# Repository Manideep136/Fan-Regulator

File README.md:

# Fan-Regulator

# Fan Regulator PCB Using KiCad

## 📌 Project Overview

This project involves designing a **Fan Regulator Circuit PCB** using KiCad. The circuit controls the speed of an AC fan by varying the power delivered to the fan using a TRIAC-based phase-control technique.

The design uses a DIAC, a TRIAC, a potentiometer, resistors, and capacitors to control the TRIAC triggering point during each AC cycle. By adjusting the potentiometer, the fan speed can be changed.

This project helps in understanding power electronics, AC phase control, schematic design, footprint assignment, and PCB layout.

## 🎯 Objectives

* Design an AC fan regulator circuit.
* Understand DIAC and TRIAC operation.
* Control fan speed using phase-angle control.
* Learn potentiometer-based adjustment.
* Create the schematic using KiCad.
* Assign footprints to electronic components.
* Design and route the PCB.
* Perform Electrical Rules Check (ERC) and Design Rules Check (DRC).
* View the completed PCB using KiCad's 3D Viewer.

## ⚙️ Working Principle

The fan regulator operates using the **TRIAC phase-control method**.

1. The AC supply voltage is applied to the regulator circuit.
2. A resistor-capacitor timing network charges during each AC half-cycle.
3. The potentiometer adjusts the charging time of the capacitor.
4. When the capacitor voltage reaches the DIAC's breakover voltage, the DIAC conducts.
5. The DIAC delivers a triggering pulse to the TRIAC gate.
6. The TRIAC conducts for the remainder of that AC half-cycle, supplying power to the fan.
7. Adjusting the potentiometer changes the TRIAC firing angle and therefore changes the power delivered to the fan.

**Note:** The exact speed-control range depends on the circuit design and the type of fan. Some modern electronic fans are not compatible with TRIAC phase control.

## 🧩 Components Used

| Reference | Component            | Function                         |
| --------- | -------------------- | -------------------------------- |
| D1        | DIAC (e.g., DB3)     | Triggers the TRIAC               |
| Q1        | TRIAC (e.g., BT136)  | Controls AC power                |
| RV1       | Potentiometer        | Adjusts the triggering point     |
| R1, R2    | Resistors            | Limit current and control timing |
| C1        | Capacitor            | Timing network                   |
| J1        | AC input connector   | Connects the AC supply           |
| J2        | Fan output connector | Connects the fan                 |

*The component values and ratings must match the actual schematic and the intended fan load.*

## 🔌 Block Diagram

```text
       AC Supply
           |
           v
     Timing Network
    (R + C + RV1)
           |
           v
          DIAC
           |
           v
      TRIAC Gate
           |
           v
   AC Fan Power Control
           |
           v
       AC Fan
```

## 🖥️ PCB Design Using KiCad

The PCB design process includes:

1. Creating the circuit schematic.
2. Adding the DIAC, TRIAC, potentiometer, resistors, and capacitor.
3. Connecting the components according to the circuit diagram.
4. Assigning suitable footprints based on the physical components.
5. Updating the PCB from the schematic.
6. Arranging the components on the PCB.
7. Routing the copper tracks.
8. Running ERC in the schematic editor.
9. Running DRC in the PCB editor.
10. Inspecting the final PCB using the 3D Viewer.

## 🔍 PCB Design Considerations

* Select footprints that match the actual DIAC, TRIAC, and potentiometer.
* Verify the TRIAC pinout using its datasheet.
* Choose resistors and capacitors with suitable voltage and power ratings.
* Use a capacitor specifically rated for its intended AC circuit position.
* Ensure adequate PCB creepage and clearance for mains voltage.
* Use suitable track widths and connectors for the fan current.
* Keep low-voltage control or accessible parts appropriately isolated from hazardous mains circuits where required.

## ✅ Advantages

* Provides adjustable fan speed.
* Uses a relatively simple electronic control circuit.
* Demonstrates practical DIAC and TRIAC applications.
* Helps develop PCB design and power-electronics skills.
* Can be adapted to compatible AC loads with a properly rated design.

## ⚠️ Safety Precautions

**This circuit may operate directly from hazardous AC mains voltage.** Its components and PCB tracks must be treated as live unless suitable isolation is provided.

* Do not touch the PCB while it is powered.
* Disconnect the supply before making adjustments or measurements.
* Do not connect a grounded oscilloscope directly to a live mains circuit.
* Use appropriate fusing, insulation, enclosure, creepage, and clearance.
* Have the design reviewed by a qualified person before connecting it to mains voltage.
* Confirm that the regulator is suitable for the specific fan type and current rating.

For initial learning, study the circuit using simulation or an appropriately isolated, low-voltage setup.

## 🚀 Future Improvements

* Add an insulated rotary control knob.
* Improve PCB layout and thermal management.
* Add appropriate input protection.
* Optimize the timing network for a compatible fan.
* Add a properly designed enclosure.
* Simulate the circuit before manufacturing the PCB.

## 📚 Learning Outcomes

Through this project, I learned:

* DIAC and TRIAC working principles.
* AC phase-angle control.
* Potentiometer-based adjustment.
* Timing networks using resistors and capacitors.
* Schematic design in KiCad.
* Footprint assignment.
* PCB component placement and routing.
* ERC and DRC verification.
* PCB design considerations for power electronics.

## 🛠️ Software Used

* **KiCad 9.0**

## 📄 License

This project is intended for educational purposes. The circuit should be reviewed and validated for electrical safety before practical use.

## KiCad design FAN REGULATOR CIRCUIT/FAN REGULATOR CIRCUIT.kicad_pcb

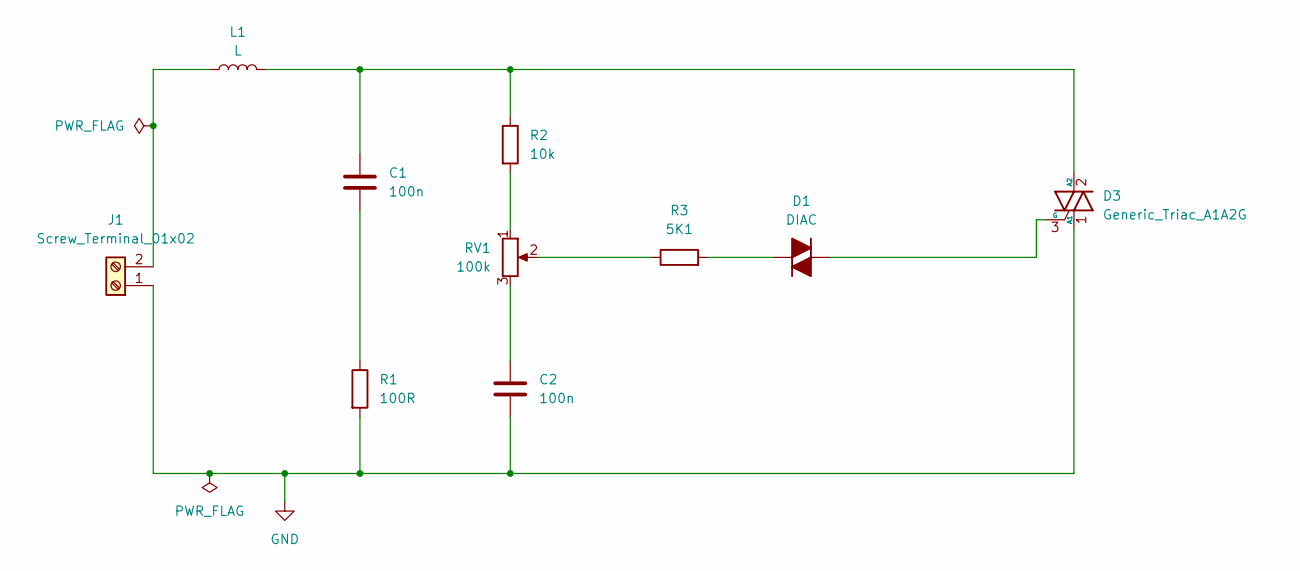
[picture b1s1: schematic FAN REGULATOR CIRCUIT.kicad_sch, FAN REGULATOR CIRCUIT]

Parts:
C1, C2: 100n; CP_Radial_D4.0mm_P1.50mm
D1: DIAC; D_DO-35_SOD27_P7.62mm_Horizontal
D3: Generic_Triac_A1A2G; TO-220-3_Vertical
J1: Screw_Terminal_01x02; TerminalBlock_Phoenix_MKDS-1,5-2-5.08_1x02_P5.08mm_Horizont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
L1: L; L_Axial_L12.8mm_D5.8mm_P5.08mm_Vertical_Fastron_HBCC
R1: 100R; R_Axial_DIN0204_L3.6mm_D1.6mm_P7.62mm_Horizontal
R2: 10k; R_Axial_DIN0204_L3.6mm_D1.6mm_P7.62mm_Horizontal
R3: 5K1; R_Axial_DIN0204_L3.6mm_D1.6mm_P7.62mm_Horizontal
RV1: 100k; Potentiometer_Alps_RK09K_Single_Horizontal

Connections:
GND: C2.2, D3.1 (A1), J1.1, R1.2
unnamed: C1.2, R1.1
unnamed: C2.1, RV1.3
unnamed: D1.2 (A), D3.3 (G)
unnamed: D1.1 (K), R3.2
unnamed: C1.1, D3.2 (A2), L1.2, R2.1
unnamed: J1.2, L1.1
unnamed: R2.2, RV1.1
unnamed: R3.1, RV1.2

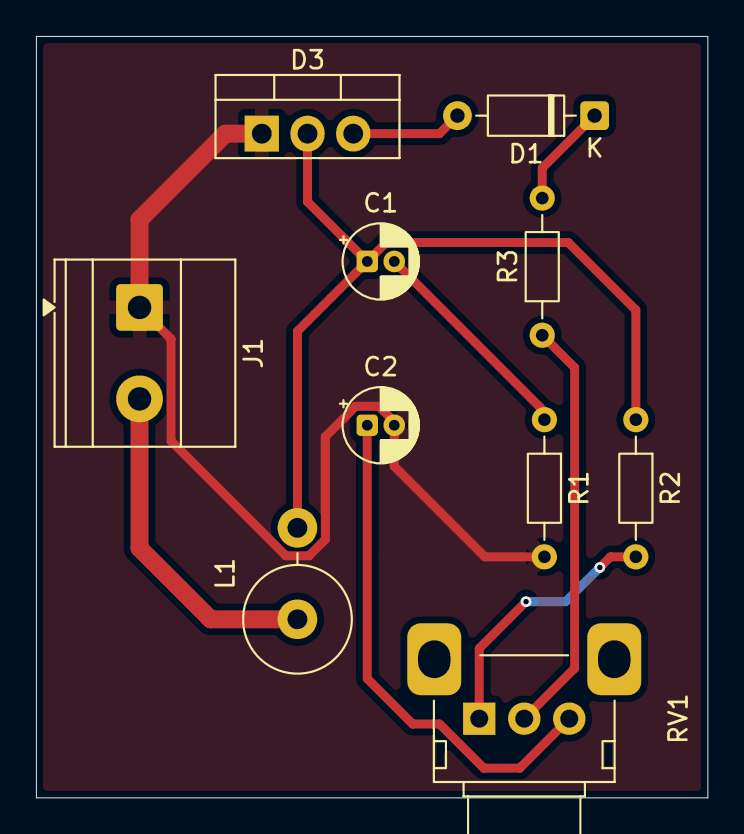
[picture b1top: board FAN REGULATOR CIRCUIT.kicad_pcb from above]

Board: 2 copper layers, 37.3 x 42.3 mm, 10 parts (0 on the bottom side), 9 nets.
